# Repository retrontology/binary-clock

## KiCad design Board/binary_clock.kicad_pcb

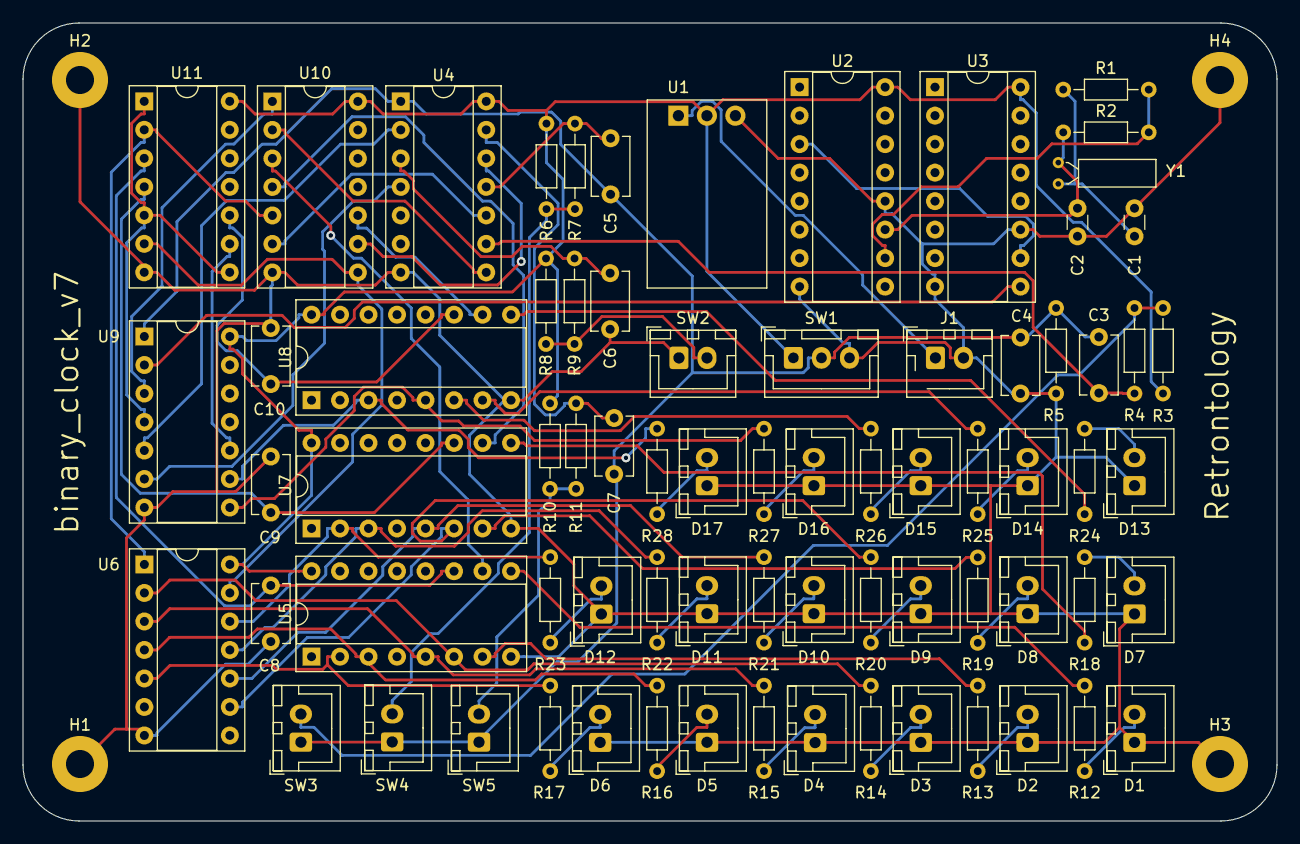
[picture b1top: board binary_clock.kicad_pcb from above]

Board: 2 copper layers, 111.8 x 71.1 mm, 77 parts (0 on the bottom side), 67 nets.

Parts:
C1, C2: 10pF; C_Disc_D3.0mm_W1.6mm_P2.50mm
C3, C4, C5, C6, C7: 100nF; C_Disc_D5.1mm_W3.2mm_P5.00mm
C8, C9, C10: 100nf; C_Disc_D5.1mm_W3.2mm_P5.00mm
D1, D2, D3, D4, D5, D6, D7, D8, D9, D10, D11, D12, D13, D14, D15, D16, D17: LED; JST_XH_B2B-XH-A_1x02_P2.50mm_Vertical
H1, H2, H3, H4: MountingHole_Pad; MountingHole_2.5mm_Pad
J1: Conn_01x02; JST_XH_B2B-XH-AM_1x02_P2.50mm_Vertical
R1: 330K; R_Axial_DIN0204_L3.6mm_D1.6mm_P7.62mm_Horizontal
R2: 10M; R_Axial_DIN0204_L3.6mm_D1.6mm_P7.62mm_Horizontal
R3, R4, R5, R6, R7, R8, R9, R10, R11: 10K; R_Axial_DIN0204_L3.6mm_D1.6mm_P7.62mm_Horizontal
R12, R13, R14, R15, R16, R17, R18, R19, R20, R21, R22, R23: 15; R_Axial_DIN0204_L3.6mm_D1.6mm_P7.62mm_Horizontal
R24, R25, R26, R27, R28: 56; R_Axial_DIN0204_L3.6mm_D1.6mm_P7.62mm_Horizontal
SW1: SW_SPST_LED; JST_XH_B3B-XH-A_1x03_P2.50mm_Vertical
SW2, SW3, SW4, SW5: SW_Push; JST_XH_B2B-XH-A_1x02_P2.50mm_Vertical
U1: OKI-78SR-3.3_1.5-W36H-C; Converter_DCDC_Murata_OKI-78SR_Horizontal
U2: CD4060BE; DIP-16_W7.62mm_Socket
U3, U5, U7, U8: 4040; DIP-16_W7.62mm_Socket
U4: 4069; DIP-14_W7.62mm_Socket
U6: 4082; DIP-14_W7.62mm_Socket
U9: 4081; DIP-14_W7.62mm_Socket
U10, U11: 4071; DIP-14_W7.62mm_Socket
Y1: 32.768KHz; Crystal_C26-LF_D2.1mm_L6.5mm_Horizontal

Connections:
+3.3V: R3.1, R6.1, R8.1, R10.1, SW1.1, U1.2 (OUT), U2.16 (VDD), U3.16 (VDD), U4.14 (Vdd), U5.16 (VDD), U6.14 (Vdd), U7.16 (VDD), U8.16 (VDD), U9.14 (Vdd), U10.14 (Vdd), U11.14 (Vdd)
+5V: J1.1, U1.1 (IN)
/Clock_1hz/CLK_1Hz: U3.9 (Q0), U9.2
/Clock_1hz/CLK_2Hz: U2.3 (Q14), U3.10 (CLK)
/Clock_Binary/CARRY_HOUR: U9.10, U11.9
/Clock_Binary/CARRY_MIN: U6.13, U10.8, U11.6
/Clock_Binary/CARRY_SEC: U6.1, U10.5, U11.2
/Clock_Binary/CLOCK_HOUR: U8.10 (CLK), U10.10
/Clock_Binary/CLOCK_MIN: U7.10 (CLK), U10.4
/Clock_Binary/CLOCK_SEC: U5.10 (CLK), U10.3
/Clock_Binary/RESET_HOUR: C10.1, U8.11 (Reset), U11.10
/Clock_Binary/RESET_MIN: C9.1, U7.11 (Reset), U11.4
/Clock_Binary/RESET_SEC: C8.1, U5.11 (Reset), U11.3
/Interface/BUTTON_HOUR: U4.12, U10.9
/Interface/BUTTON_MIN: U4.10, U10.6
/Interface/BUTTON_RESET: U4.4, U9.6
/Interface/BUTTON_SEC: U4.8, U10.2
/Interface/SWITCH_PAUSE: U4.2, U9.5
/Interface/SWITCH_PAUSE_NOT: C3.2, C4.1, C5.2, C7.2, R5.1, SW1.2, SW3.1, SW4.1, SW5.1, U4.1, U9.1
GND: C1.2, C2.2, C4.2, C6.2, C8.2, C9.2, C10.2, D1.1 (K), D2.1 (K), D3.1 (K), D4.1 (K), D5.1 (K), D6.1 (K), D7.1 (K), D8.1 (K), D9.1 (K), D10.1 (K), D11.1 (K), D12.1 (K), D13.1 (K), D14.1 (K), D15.1 (K), D16.1 (K), D17.1 (K), H1.1, H2.1, H3.1, H4.1, J1.2, R5.2, SW1.3 (K), SW2.1, U1.3 (GND), U2.8 (VSS), U2.12 (RESET), U3.8 (VSS), U3.11 (Reset), U4.7 (Vss), U5.8 (VSS), U6.7 (Vss), U7.8 (VSS), U8.8 (VSS), U9.7 (Vss), U10.7 (Vss), U11.7 (Vss)
unnamed: C1.1, R1.1, Y1.1
unnamed: C3.1, R4.2, U4.9
unnamed: C5.1, R7.2, U4.11
unnamed: C6.1, R9.2, U4.3
unnamed: C7.1, R11.2, U4.13
unnamed: D1.2 (A), R12.1
unnamed: D2.2 (A), R13.1
unnamed: D3.2 (A), R14.1
unnamed: D4.2 (A), R15.1
unnamed: D5.2 (A), R16.1
unnamed: D6.2 (A), R17.1
unnamed: D7.2 (A), R18.1
unnamed: D8.2 (A), R19.1
unnamed: D9.2 (A), R20.1
unnamed: D10.2 (A), R21.1
unnamed: D11.2 (A), R22.1
unnamed: D12.2 (A), R23.1
unnamed: D13.2 (A), R24.1
unnamed: D14.2 (A), R25.1
unnamed: D15.2 (A), R26.1
unnamed: D16.2 (A), R27.1
unnamed: D17.2 (A), R28.1
unnamed: R3.2, R4.1, SW3.2
unnamed: R6.2, R7.1, SW4.2
unnamed: R8.2, R9.1, SW2.2
unnamed: R10.2, R11.1, SW5.2
unnamed: C2.1, R2.2, U2.11 ((PHI)I), Y1.2
unnamed: R1.2, R2.1, U2.10 (~(PHI)O)
unnamed: R12.2, U5.9 (Q0)
unnamed: R13.2, U5.7 (Q1)
unnamed: R14.2, U5.6 (Q2), U6.2
unnamed: R15.2, U5.5 (Q3), U6.3
unnamed: R16.2, U5.3 (Q4), U6.4
unnamed: R17.2, U5.2 (Q5), U6.5
unnamed: R18.2, U7.9 (Q0)
unnamed: R19.2, U7.7 (Q1)
unnamed: R20.2, U6.9, U7.6 (Q2)
unnamed: R21.2, U6.10, U7.5 (Q3)
unnamed: R22.2, U6.11, U7.3 (Q4)
unnamed: R23.2, U6.12, U7.2 (Q5)
unnamed: R24.2, U8.9 (Q0)
unnamed: R25.2, U8.7 (Q1)
unnamed: R26.2, U8.6 (Q2)
unnamed: R27.2, U8.5 (Q3), U9.8
unnamed: R28.2, U8.3 (Q4), U9.9
unnamed: U9.3, U10.1
unnamed: U9.4, U11.1, U11.5, U11.8

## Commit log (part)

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2023-04-19 fix 3.3v regulator footprint
2023-04-19 add caps to all resets
2023-04-19 add branding and version silkscreen
